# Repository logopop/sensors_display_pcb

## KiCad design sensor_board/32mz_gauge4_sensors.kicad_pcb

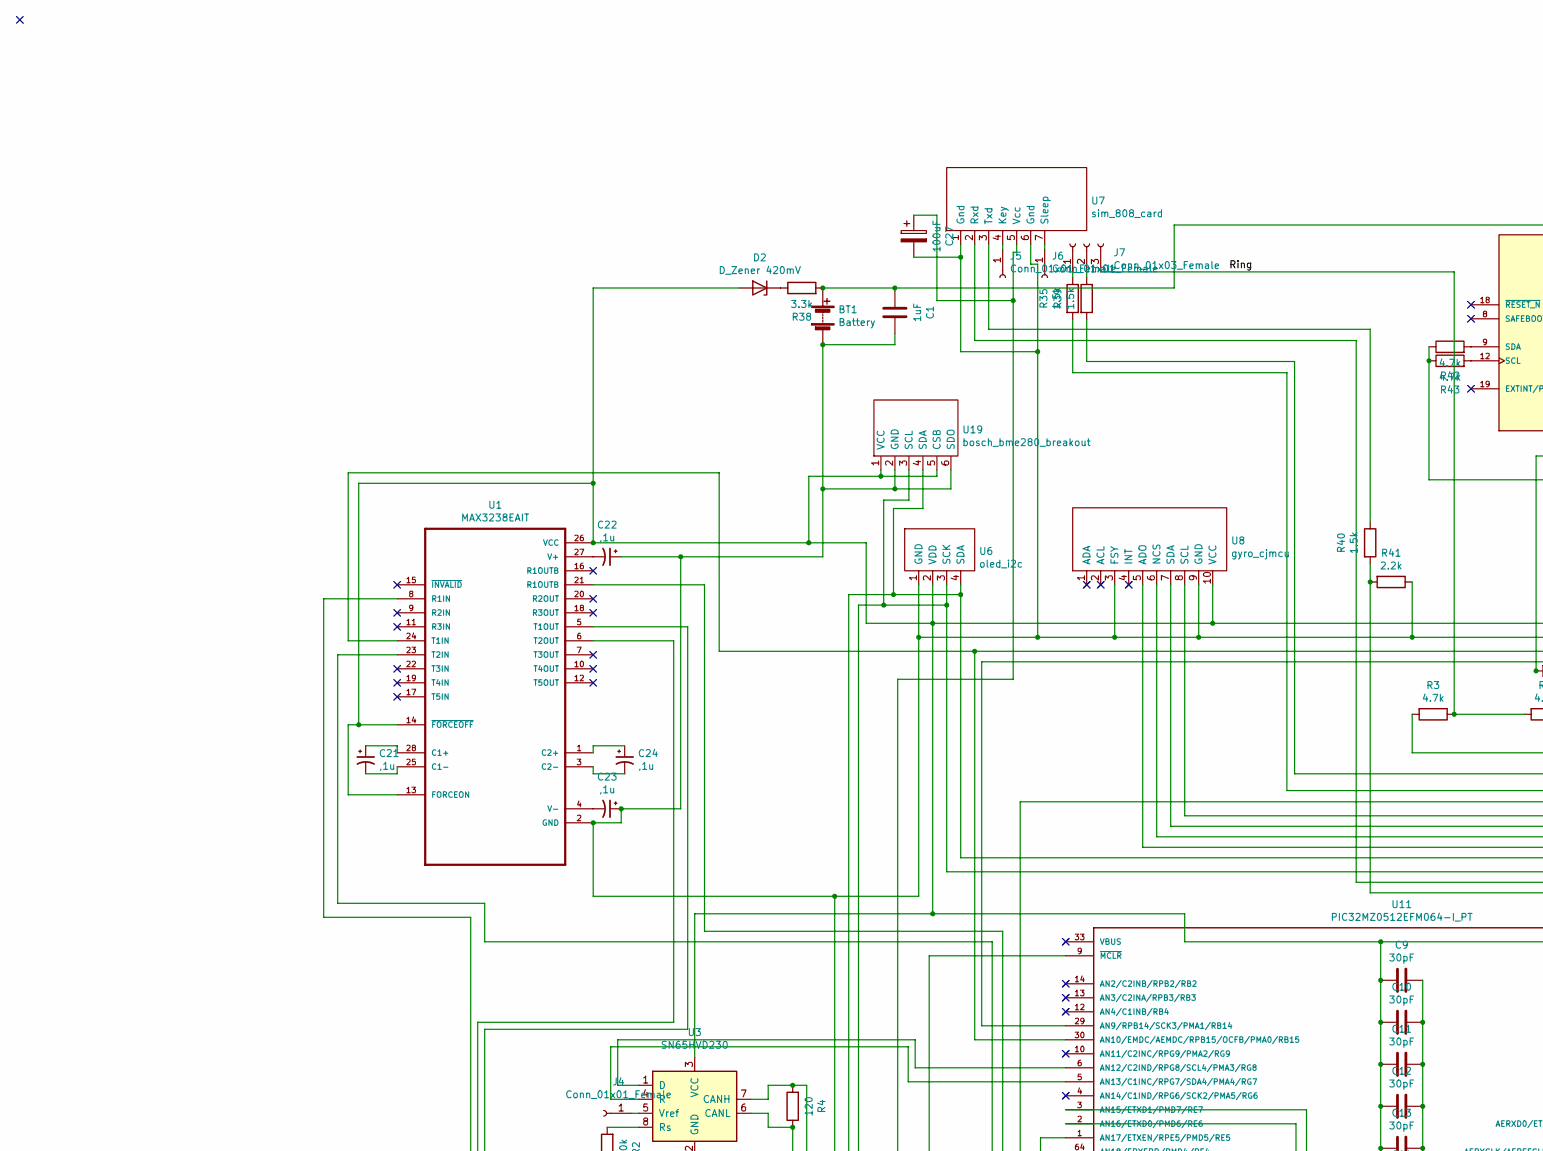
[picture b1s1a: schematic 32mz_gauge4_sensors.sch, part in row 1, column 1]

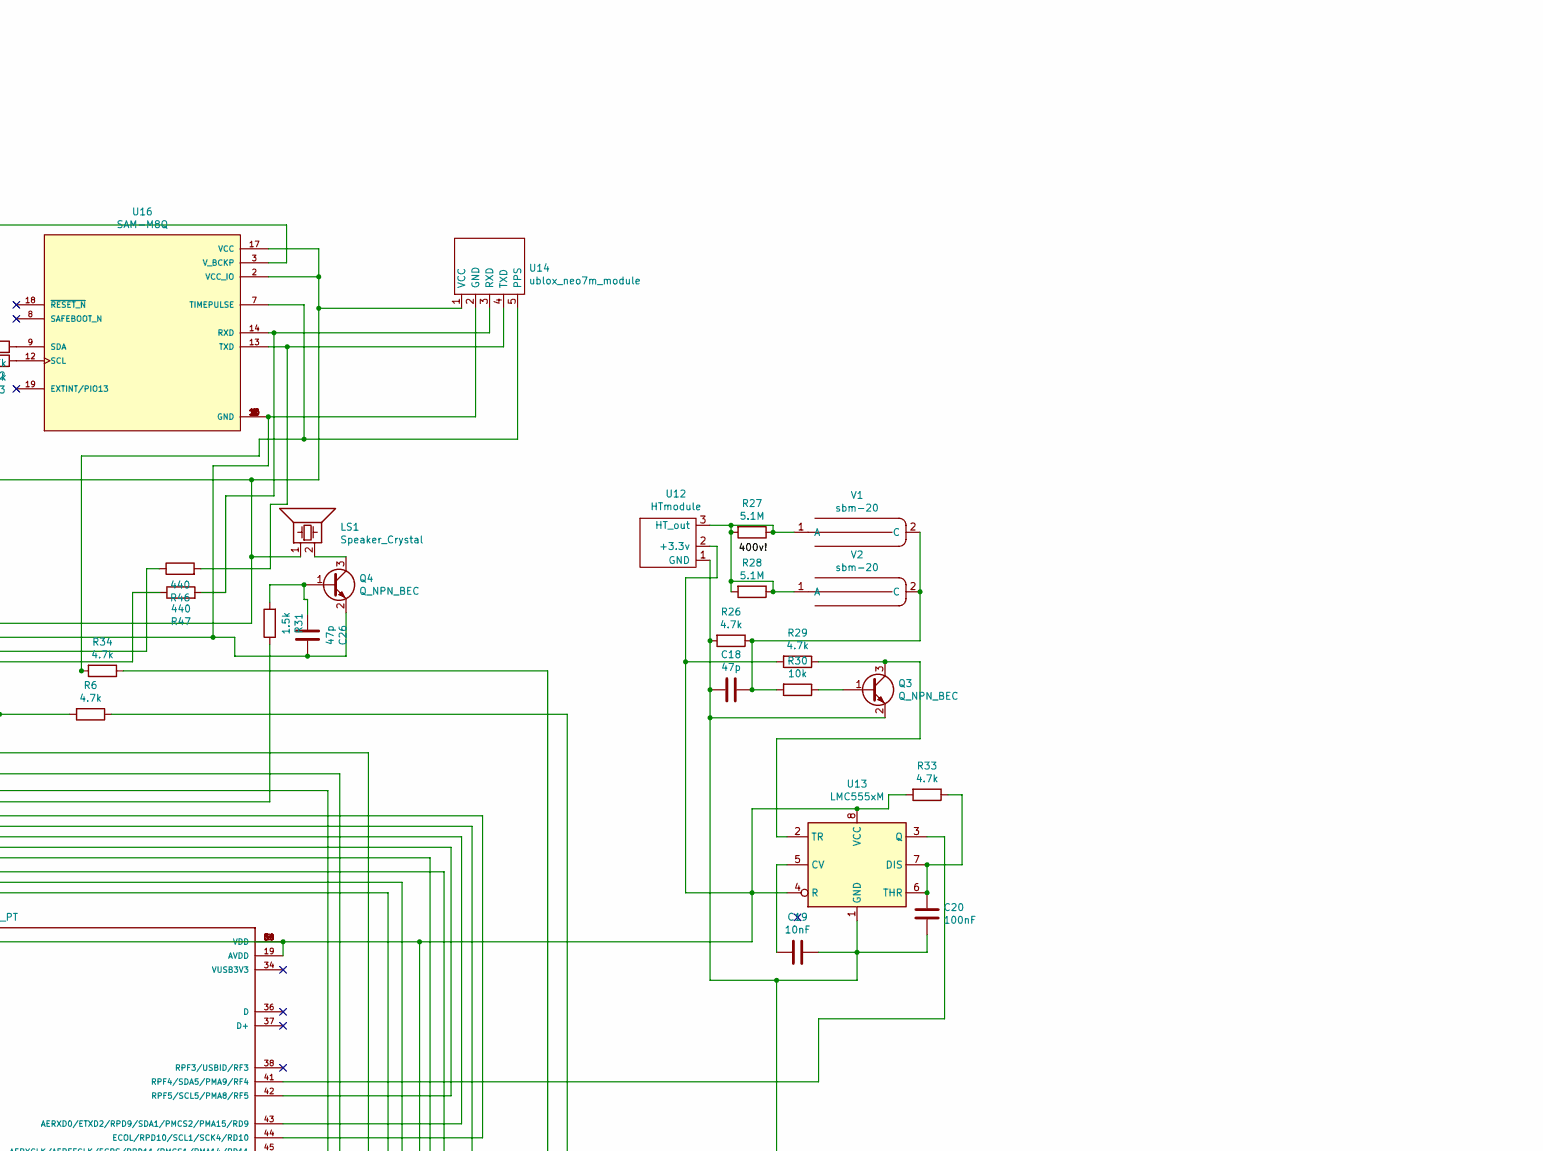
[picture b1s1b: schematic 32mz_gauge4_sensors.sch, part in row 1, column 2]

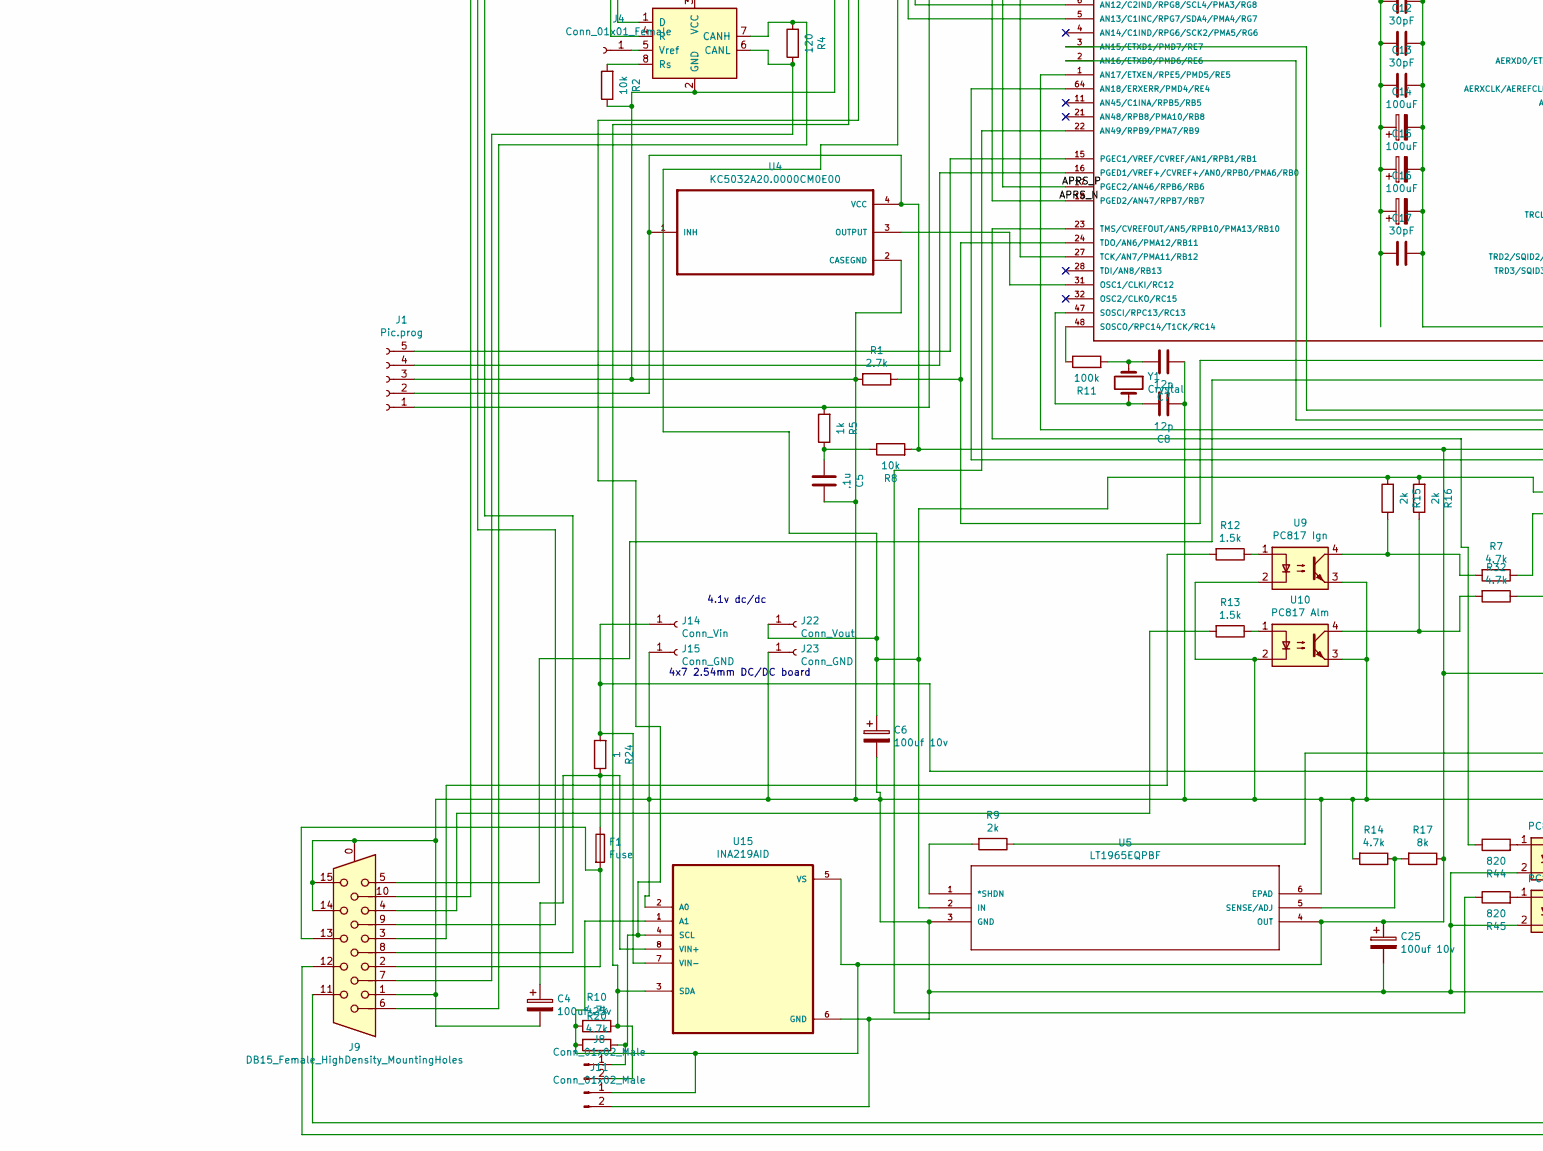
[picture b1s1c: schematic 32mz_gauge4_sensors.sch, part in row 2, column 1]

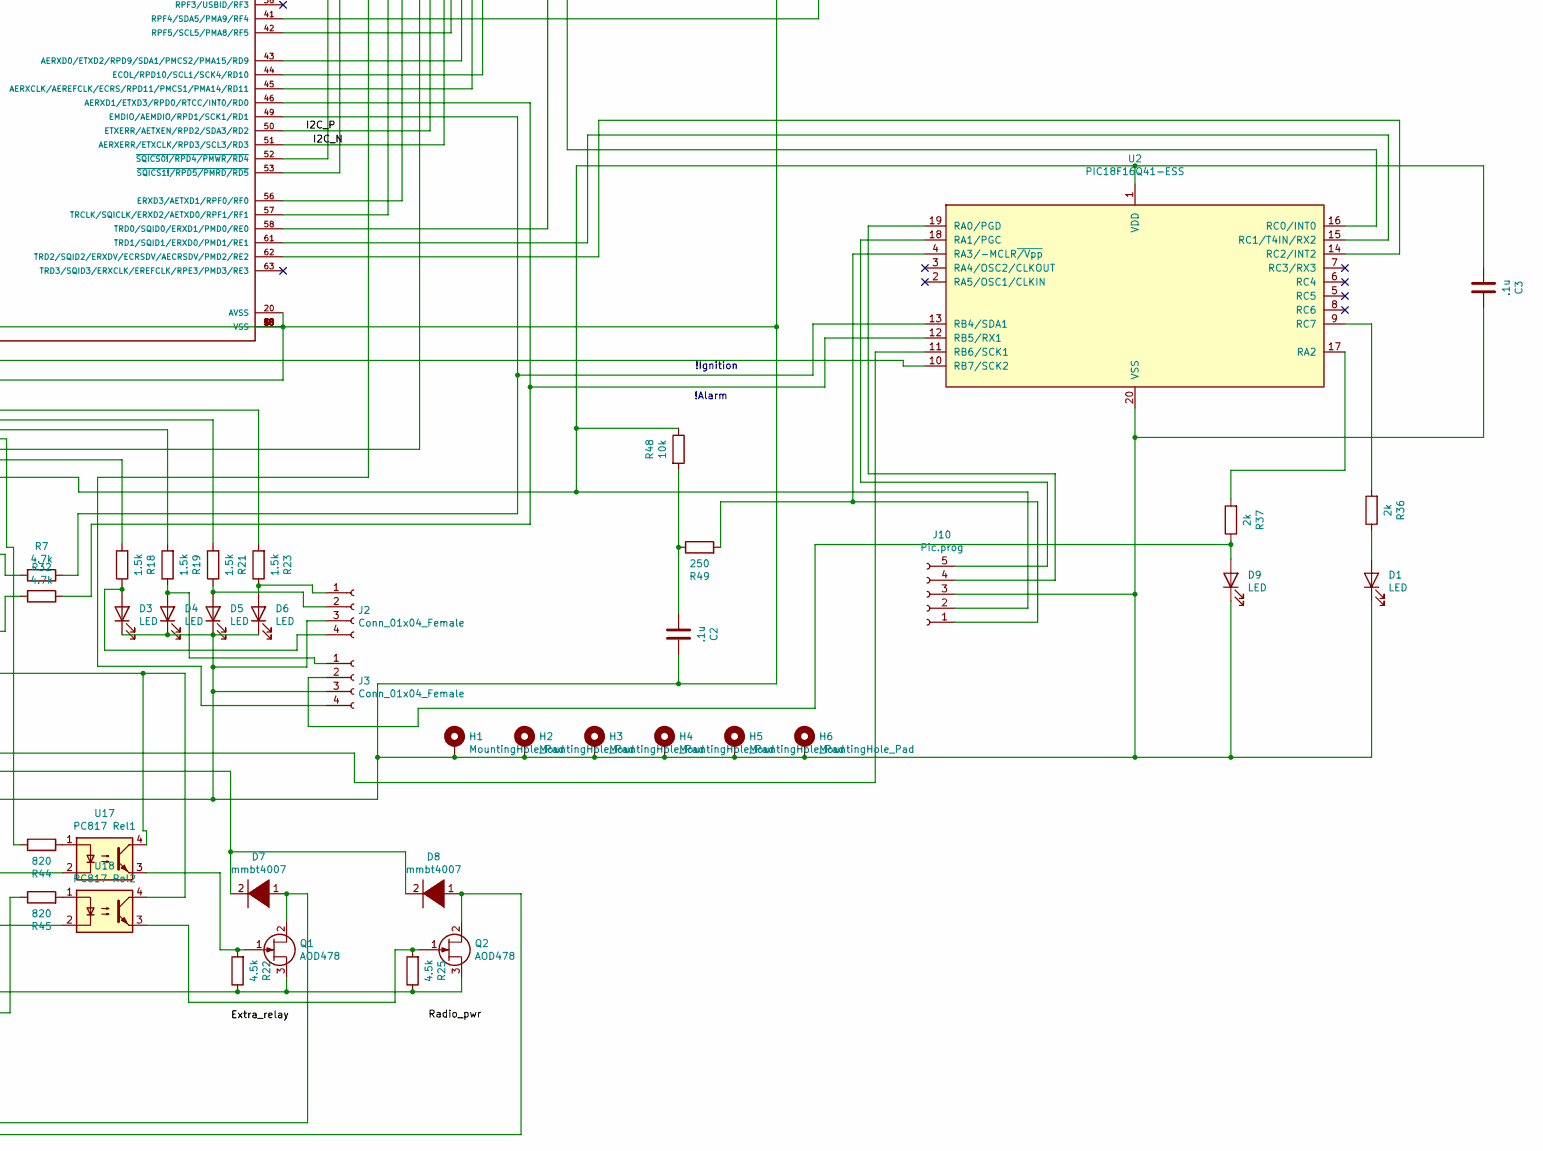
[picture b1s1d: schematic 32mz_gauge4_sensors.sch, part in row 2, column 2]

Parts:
BT1: Battery; batt_holder_1220
C1: 1uF; C_0805_2012Metric_Pad1.15x1.40mm_HandSolder
C2, C3, C5: .1u; C_0603_1608Metric_Pad1.05x0.95mm_HandSolder
C4: 100uf 25v; CP_EIA-6032-28_Kemet-C_Pad2.25x2.35mm_HandSolder
C6: 100uf 10v; CP_EIA-6032-20_AVX-F_Pad2.25x2.35mm_HandSolder
C7, C8: 12p; C_0603_HandSoldering
C9, C10, C11, C12, C13, C17: 30pF; C_0603_HandSoldering
C14, C15, C16, C27: 100uF; CP_EIA-6032-15_Kemet-U_Pad2.25x2.35mm_HandSolder
C18, C26: 47p; C_0603_HandSoldering
C19: 10nF; C_0603_HandSoldering
C20: 100nF; C_0603_HandSoldering
C21, C22, C23, C24: ,1u; C_1812_4532Metric_Pad1.30x3.40mm_HandSolder
C25: 100uf 10v; CP_EIA-6032-28_Kemet-C_Pad2.25x2.35mm_HandSolder
D1, D3, D4, D5, D6, D9: LED; LED_0603_1608Metric_Pad1.05x0.95mm_HandSolder
D2: D_Zener 420mV; D_1806_4516Metric_Pad1.57x1.80mm_HandSolder
D7, D8: mmbt4007; D_3220_8050Metric_Pad2.65x5.15mm_HandSolder
F1: Fuse; Fuseholder5x20_horiz_open_inline_Type-I
H1, H2, H3, H4, H5, H6: MountingHole_Pad; MountingHole_2.7mm_M2.5_ISO14580_Pad
J1: Pic.prog; Pin_Header_Straight_1x05_Pitch2.00mm
J2, J3: Conn_01x04_Female; PinHeader_1x04_P2.00mm_Vertical
J4: Conn_01x01_Female; Pin_Header_Straight_1x01_Pitch2.54mm
J5, J6: Conn_01x01_Female; PinHeader_1x01_P2.54mm_Vertical
J7: Conn_01x03_Female; PinHeader_1x03_P2.00mm_Vertical
J8, J11: Conn_01x02_Male; PinHeader_1x02_P2.54mm_Vertical
J9: DB15_Female_HighDensity_MountingHoles; DSUB-15-HD_Female_Horizontal_P2.29x1.98mm_EdgePinOffset3.03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
J10: Pic.prog; PinSocket_1x05_P2.00mm_Vertical
J14: Conn_Vin; PinHeader_1x01_P2.00mm_Vertical
J15, J23: Conn_GND; PinHeader_1x01_P2.00mm_Vertical
J22: Conn_Vout; PinHeader_1x01_P2.00mm_Vertical
LS1: Speaker_Crystal; Pin_Header_Straight_1x02_Pitch2.54mm
Q1, Q2: AOD478; TO-252-2
Q3, Q4: Q_NPN_BEC; SC-59_Handsoldering
R1: 2.7k; R_0805_2012Metric_Pad1.15x1.40mm_HandSolder
R2, R8, R30, R48: 10k; R_0805_2012Metric_Pad1.15x1.40mm_HandSolder
R3, R6, R7, R10, R14, R20, R26, R29, R32, R33, R34, R42, R43: 4.7k; R_0805_2012Metric_Pad1.15x1.40mm_HandSolder
R4: 120; R_0805_2012Metric_Pad1.15x1.40mm_HandSolder
R5: 1k; R_0805_2012Metric_Pad1.15x1.40mm_HandSolder
R9, R15, R16, R36, R37: 2k; R_0805_2012Metric_Pad1.15x1.40mm_HandSolder
R11: 100k; R_0805_2012Metric_Pad1.15x1.40mm_HandSolder
R12, R13, R18, R19, R21, R23, R31, R35, R39, R40: 1.5k; R_0805_2012Metric_Pad1.15x1.40mm_HandSolder
R17: 8k; R_0805_2012Metric_Pad1.15x1.40mm_HandSolder
R22, R25: 4.5k; R_0805_2012Metric_Pad1.15x1.40mm_HandSolder
R24: 1; R_2816_7142Metric_Pad3.20x4.45mm_HandSolder
R27, R28: 5.1M; R_0805_2012Metric_Pad1.15x1.40mm_HandSolder
R38: 3.3k; R_0805_2012Metric_Pad1.15x1.40mm_HandSolder
R41: 2.2k; R_0805_2012Metric_Pad1.15x1.40mm_HandSolder
R44, R45: 820; R_0805_2012Metric_Pad1.15x1.40mm_HandSolder
R46, R47: 440; R_0805_2012Metric_Pad1.15x1.40mm_HandSolder
R49: 250; R_0805_2012Metric_Pad1.15x1.40mm_HandSolder
U1: MAX3238EAIT; SSOP-28_5.3x10.2mm_Pitch0.65mm
U2: PIC18F16Q41-ESS; SSOP-20_5.3x7.2mm_P0.65mm_mod
U3: SN65HVD230; HTSOP-8-1EP_3.9x4.9mm_Pitch1.27mm_LargeCopper
U4: KC5032A20.0000CM0E00; Oscillator_SMD_EuroQuartz_XO53-4pin_5.0x3.2mm_HandSoldering
U5: LT1965EQPBF; DDPAK-5_Q
U6: oled_i2c; PinHeader_1x04_P2.54mm_Vertical
U7: sim_808_card; gsm_module_2
U8: gyro_cjmcu
U9: PC817 Ign; SOT254P975X400-4N
U10: PC817 Alm; SOT254P975X400-4N
U11: PIC32MZ0512EFM064-I_PT; TQFP-64-1EP_10x10mm_Pitch0.5mm
U12: HTmodule; HT_module
U13: LMC555xM; SOP-8_5.28x5.23mm_P1.27mm
U14: ublox_neo7m_module
U15: INA219AID; SOIC127P599X175-8N
U16: SAM-M8Q; XCVR_SAM-M8Q; PARTREV R06
U17: PC817 Rel1; SOT254P975X400-4N
U18: PC817 Rel2; SOT254P975X400-4N
U19: bosch_bme280_breakout
V1, V2: sbm-20; sbm_20
Y1: Crystal; Crystal_DS15_d1.5mm_l5.0mm_Vertical

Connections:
/APRS_N: U1.23 (T2IN), U11.18 (PGED2/AN47/RPB7/RB7)
/APRS_P: U1.21 (R1OUTB), U11.17 (PGEC2/AN46/RPB6/RB6)
/I2C_N: J8.1, R20.1, U6.3 (SCK), U11.51 (AERXERR/ETXCLK/RPD3/SCL3/RD3), U15.4 (SCL), U19.3 (SCL)
/I2C_P: J8.2, R10.1, U6.4 (SDA), U11.50 (ETXERR/AETXEN/RPD2/SDA3/RD2), U15.3 (SDA), U19.4 (SDA)
unnamed: BT1.1 (+), C1.1, R38.2, U16.3 (V_BCKP)
unnamed: BT1.2 (-), C1.2, C2.2, C3.2, C4.2, C5.2, C6.2, C7.1, C8.1, C9.2, C10.2, C11.2, C12.2, C13.2, C14.2, C15.2, C16.2, C17.2, C18.2, C19.1, C20.1, C22.1, C23.1, C25.2, C26.1, C27.2, D1.1 (K), D3.1 (K), D4.1 (K), D5.1 (K), D6.1 (K), D9.1 (K), H1.1, H2.1, H3.1, H4.1, H5.1, H6.1, J1.3, J2.3, J3.3, J9.0, J9.1, J9.5, J9.14, J9.15, J10.3, J11.2, J15.1, J23.1, Q1.3 (S), Q2.3 (S), Q3.2 (E), Q4.2 (E), R1.2, R2.1, R14.2, R22.1, R25.1, R26.2, R41.1, U1.2 (GND), U2.20 (VSS), U3.2 (GND), U4.2 (CASEGND), U5.3 (GND), U5.6 (EPAD), U6.1 (GND), U7.1 (Gnd), U7.6 (Gnd), U8.3 (FSY), U8.9 (GND), U9.2, U9.3, U10.2, U10.3, U11.7 (VSS), U11.20 (AVSS), U11.25 (VSS), U11.35 (VSS), U11.40 (VSS), U11.55 (VSS), U11.59 (VSS), U12.1 (GND), U13.1 (GND), U14.2 (GND), U15.2 (A0), U15.6 (GND), U16.1 (GND), U16.4 (GND), U16.5 (GND), U16.6 (GND), U16.10 (GND), U16.11 (GND), U16.15 (GND), U16.16 (GND), U16.20 (GND), U17.2, U18.2, U19.2 (GND), U19.6 (SDO)
unnamed: C2.1, R48.2, R49.1
unnamed: C4.1, F1.1, R24.1, U15.8 (VIN+)
unnamed: C5.1, R5.1, R8.1
unnamed: C7.2, R11.2, Y1.1
unnamed: C8.2, U11.47 (SOSCI/RPC13/RC13), Y1.2
unnamed: C9.1, C10.1, C11.1, C12.1, C13.1, C14.1, C15.1, C16.1, C17.1, C25.1, D2.2 (A), J1.2, J11.1, LS1.1, R8.2, R10.2, R17.1, R20.2, R29.2, R33.2, R42.1, R43.1, U1.13 (FORCEON), U1.14 (~FORCEOFF~), U1.26 (VCC), U3.3 (VCC), U4.1 (INH), U4.4 (VCC), U5.4 (OUT), U6.2 (VDD), U8.10 (VCC), U11.8 (VDD), U11.19 (AVDD), U11.26 (VDD), U11.39 (VDD), U11.54 (VDD), U11.60 (VDD), U12.2 (+3.3v), U13.4 (R), U13.8 (VCC), U14.1 (VCC), U15.1 (A1), U15.5 (VS), U16.2 (VCC_IO), U16.17 (VCC), U17.4, U18.4, U19.1 (VCC), U19.5 (CSB)
unnamed: C18.1, R26.1, R30.2, V1.2 (C), V2.2 (C)
unnamed: C19.2, U13.5 (CV)
unnamed: C20.2, R33.1, U13.6 (THR), U13.7 (DIS)
unnamed: C21.1, U1.28 (C1+)
unnamed: C21.2, U1.25 (C1-)
unnamed: C22.2, U1.27 (V+)
unnamed: C23.2, U1.4 (V-)
unnamed: C24.1, U1.1 (C2+)
unnamed: C24.2, U1.3 (C2-)
unnamed: C26.2, Q4.1 (B), R31.2
unnamed: C3.1, C6.1, C27.1, J10.2, J22.1, R15.2, R16.2, R48.1, U2.1 (VDD), U5.2 (IN), U7.5 (Vcc)
unnamed: D1.2 (A), R36.1
unnamed: D2.1 (K), R38.1
unnamed: D3.2 (A), J2.4, R18.1
unnamed: D4.2 (A), J3.1, R19.1
unnamed: D5.2 (A), J2.2, R21.1
unnamed: D6.2 (A), J2.1, R23.1
unnamed: D7.1 (K), J9.11, Q1.2 (D)
unnamed: D7.2 (A), D8.2 (A), J14.1, R24.2, U15.7 (VIN-)
unnamed: D8.1 (K), J9.12, Q2.2 (D)
unnamed: D9.2 (A), J3.2, R37.1
unnamed: F1.2, J9.2, J9.13
unnamed: J1.1, R5.2, U11.9 (~MCLR~)
unnamed: J1.4, U11.16 (PGED1/VREF+/CVREF+/AN0/RPB0/PMA6/RB0)
unnamed: J1.5, U11.15 (PGEC1/VREF/CVREF/AN1/RPB1/RB1)
unnamed: J3.4, R3.2
unnamed: J4.1, U3.5 (Vref)
unnamed: J5.1, U7.4 (Key)
unnamed: J6.1, U7.7 (Sleep)
unnamed: J7.1, R35.1
unnamed: J7.2, R39.1
unnamed: J7.3, R3.1, R6.2
unnamed: J9.3, R12.2
unnamed: J9.4, R13.2
unnamed: J9.6, R4.2, U3.7 (CANH)
unnamed: J9.7, R4.1, U3.6 (CANL)
unnamed: J9.8, U1.5 (T1OUT)
unnamed: J9.9, U1.6 (T2OUT)
unnamed: J9.10, U1.8 (R1IN)
unnamed: J10.1, R49.2, U2.4 (RA3/-MCLR~/Vpp)
unnamed: J10.4, U2.19 (RA0/PGD)
unnamed: J10.5, U2.18 (RA1/PGC)
unnamed: LS1.2, Q4.3 (C)
unnamed: Q1.1 (G), R22.2, U17.3
unnamed: Q2.1 (G), R25.2, U18.3
unnamed: Q3.1 (B), R30.1
unnamed: Q3.3 (C), R29.1, U13.2 (TR)
unnamed: R1.1, U2.10 (RB7/SCK2), U11.24 (TDO/AN6/PMA12/RB11)
unnamed: R2.2, U3.8 (Rs)
unnamed: R6.1, U2.16 (RC0/INT0)
unnamed: R7.1, U2.13 (RB4/SDA1), U11.49 (EMDIO/AEMDIO/RPD1/SCK1/RD1)
unnamed: R9.1, U2.11 (RB6/SCK1)
unnamed: R9.2, U5.1 (*SHDN)
unnamed: R11.1, U11.48 (SOSCO/RPC14/T1CK/RC14)
unnamed: R12.1, U9.1
unnamed: R13.1, U10.1
unnamed: R14.1, R17.2, U5.5 (SENSE/ADJ)
unnamed: R7.2, R15.1, U9.4
unnamed: R16.1, R32.2, U10.4
unnamed: R18.2, U11.64 (AN18/ERXERR/PMD4/RE4)
unnamed: R19.2, U11.1 (AN17/ETXEN/RPE5/PMD5/RE5)
unnamed: R21.2, U11.2 (AN16/ETXD0/PMD6/RE6)
unnamed: R23.2, U11.3 (AN15/ETXD1/PMD7/RE7)
unnamed: R27.1, R27.2, R28.1, R28.2, U12.3 (HT_out), V1.1 (A), V2.1 (A)
unnamed: R31.1, U11.27 (TCK/AN7/PMA11/RB12)
unnamed: R32.1, U2.12 (RB5/RX1), U11.46 (AERXD1/ETXD3/RPD0/RTCC/INT0/RD0)
unnamed: R34.1, U11.58 (TRD0/SQID0/ERXD1/PMD0/RE0)
unnamed: R34.2, U14.5 (PPS), U16.7 (TIMEPULSE)
unnamed: R35.2, U11.52 (~SQICS0!/RPD4/PMWR/RD4~)
unnamed: R36.2, U2.9 (RC7)
unnamed: R37.2, U2.17 (RA2)
unnamed: R39.2, U11.53 (~SQICS1!/RPD5/PMRD/RD5~)
unnamed: R40.1, U7.3 (Txd)
unnamed: R40.2, R41.2, U11.57 (TRCLK/SQICLK/ERXD2/AETXD0/RPF1/RF1)
unnamed: R42.2, U16.9 (SDA)
unnamed: R43.2, U16.12 (SCL)
unnamed: R44.1, U11.23 (TMS/CVREFOUT/AN5/RPB10/PMA13/RB10)
unnamed: R44.2, U17.1
unnamed: R45.1, U11.22 (AN49/RPB9/PMA7/RB9)
unnamed: R45.2, U18.1
unnamed: R46.1, U1.24 (T1IN), U11.30 (AN10/EMDC/AEMDC/RPB15/OCFB/PMA0/RB15)
unnamed: R46.2, U14.4 (TXD), U16.13 (TXD)
unnamed: R47.1, U11.29 (AN9/RPB14/SCK3/PMA1/RB14)
unnamed: R47.2, U14.3 (RXD), U16.14 (RXD)
unnamed: U3.4 (R), U11.5 (AN13/C1INC/RPG7/SDA4/PMA4/RG7)
unnamed: U3.1 (D), U11.6 (AN12/C2IND/RPG8/SCL4/PMA3/RG8)
unnamed: U4.3 (OUTPUT), U11.31 (OSC1/CLKI/RC12)
unnamed: U11.41 (RPF4/SDA5/PMA9/RF4), U13.3 (Q)
unnamed: U8.5 (ADO), U11.42 (RPF5/SCL5/PMA8/RF5)
unnamed: U8.6 (NCS), U11.43 (AERXD0/ETXD2/RPD9/SDA1/PMCS2/PMA15/RD9)
unnamed: U8.8 (SCL), U11.44 (ECOL/RPD10/SCL1/SCK4/RD10)
unnamed: U8.7 (SDA), U11.45 (AERXCLK/AEREFCLK/ECRS/RPD11/PMCS1/PMA14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)
unnamed: U7.2 (Rxd), U11.56 (ERXD3/AETXD1/RPF0/RF0)
unnamed: U2.15 (RC1/T4IN/RX2), U11.61 (TRD1/SQID1/ERXD0/PMD1/RE1)
unnamed: U2.14 (RC2/INT2), U11.62 (TRD2/SQID2/ERXDV/ECRSDV/AECRSDV/PMD2/RE2)

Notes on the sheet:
4x7 2.54mm DC/DC board
!Alarm
!Ignition
4.1v dc/dc

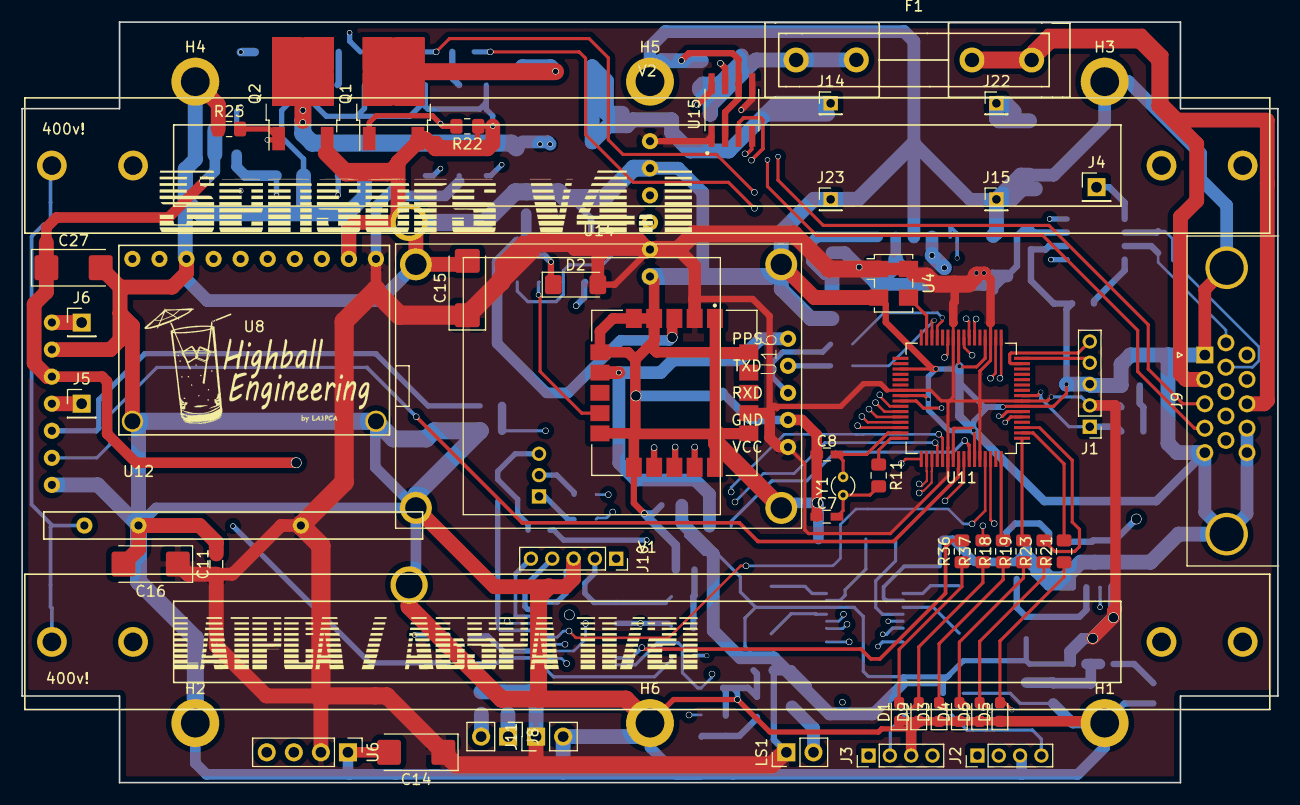
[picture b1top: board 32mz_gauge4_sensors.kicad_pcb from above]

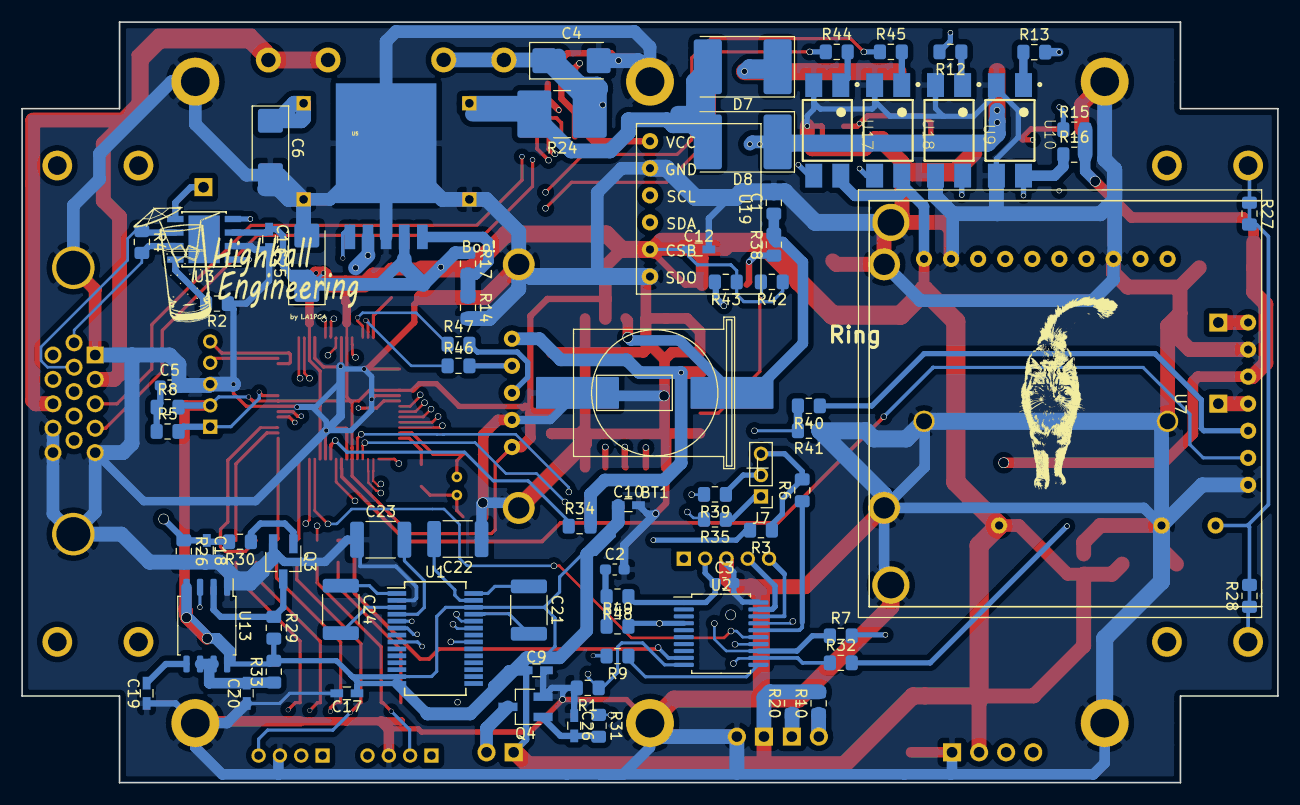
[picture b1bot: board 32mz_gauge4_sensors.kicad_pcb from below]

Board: 4 copper layers, 117.9 x 71.4 mm, 136 parts (78 on the bottom side), 107 nets.

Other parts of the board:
 : fry

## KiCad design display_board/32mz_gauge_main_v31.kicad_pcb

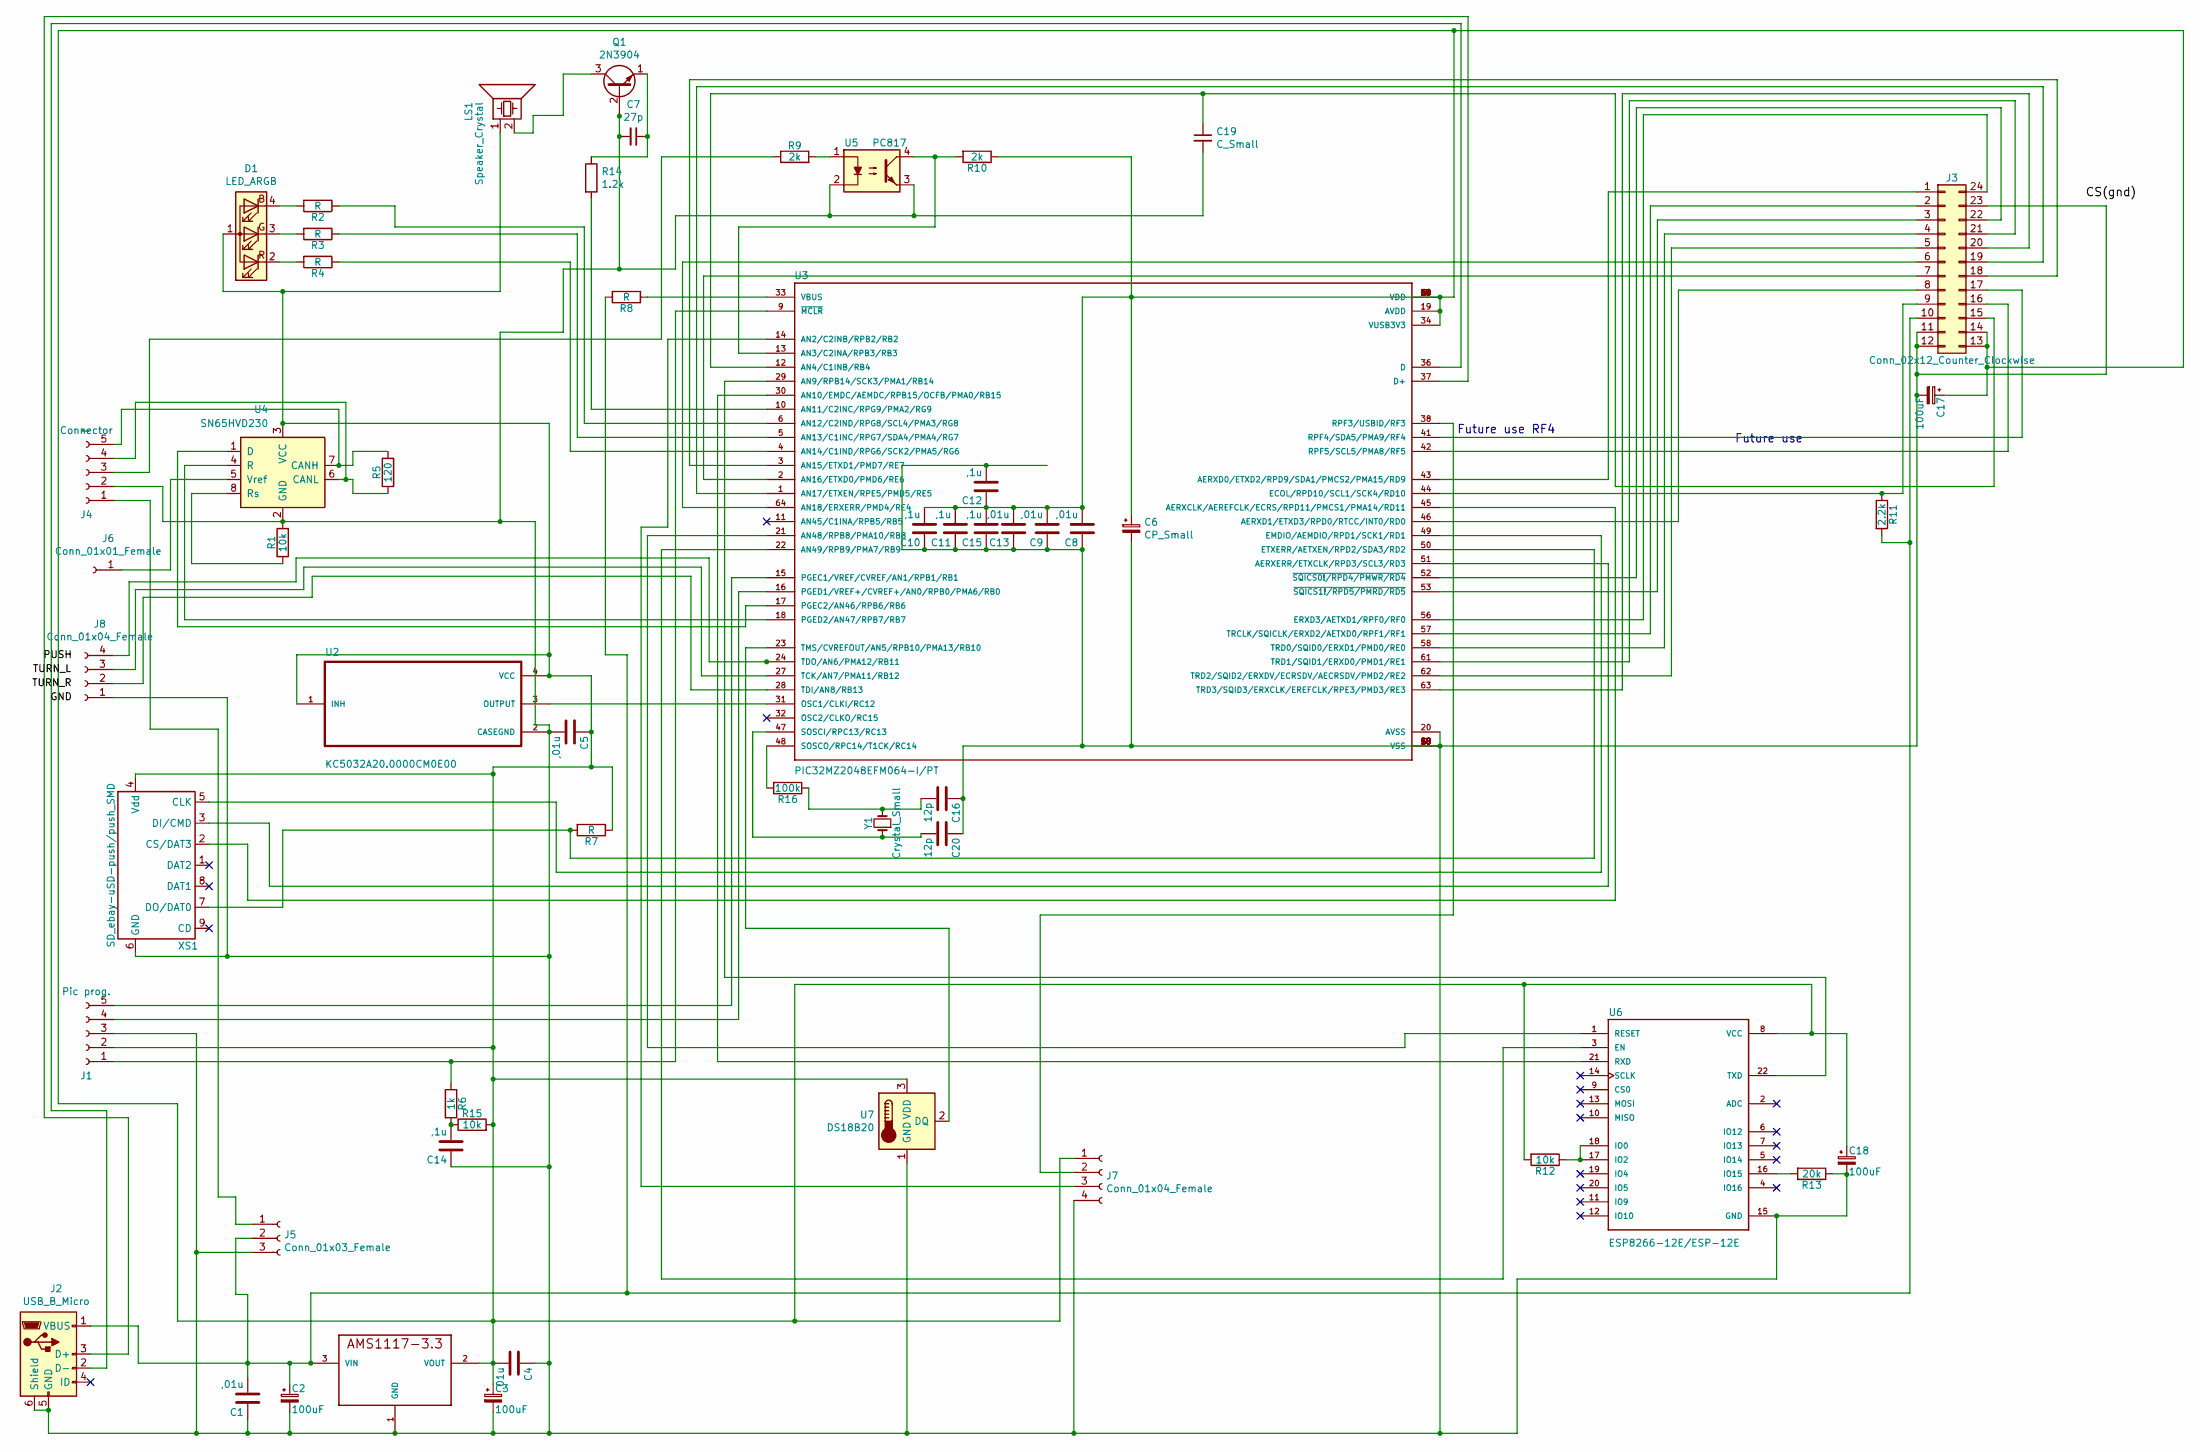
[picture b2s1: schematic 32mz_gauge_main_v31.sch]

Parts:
C1, C4, C5: ,01u; C_0805_HandSoldering
C2, C3: 100uF; CP_Elec_5x4.5
C6: CP_Small; CP_Tantalum_Case-A_EIA-3216-18_Hand
C7: 27p; C_0603_HandSoldering
C8, C9, C13: ,01u; C_0603_HandSoldering
C10, C11, C12, C14, C15: ,1u; C_0603_HandSoldering
C16, C20: 12p; C_0603_HandSoldering
C17, C18: 100uF; CP_Tantalum_Case-A_EIA-3216-18_Hand
C19: C_Small; C_0603_HandSoldering
D1: LED_ARGB; SM0605BCRG
J1: Pic prog.; Pin_Header_Straight_1x05_Pitch2.00mm
J2: USB_B_Micro; USB_Micro-B_Molex-105017-0001
J3: Conn_02x12_Counter_Clockwise; JAE_LY20-24P-2T_2x12x2.00mm_Straight
J4: Connector; JST_ZE_BM05B-ZESS-TBT_05x1.5mm_Straight
J5: Conn_01x03_Female; Pin_Header_Straight_1x03_Pitch2.54mm
J6: Conn_01x01_Female; Pin_Header_Straight_1x01_Pitch1.00mm
J7: Conn_01x04_Female; Pin_Header_Straight_1x04_Pitch2.00mm
J8: Conn_01x04_Female; JST_ZE_BM04B-ZESS-TBT_04x1.5mm_Straight
LS1: Speaker_Crystal; Pin_Header_Straight_1x02_Pitch2.00mm
Q1: 2N3904; SOT-23
R1, R12, R15: 10k; R_0603_HandSoldering
R2, R3, R4, R7, R8: R; R_0603_HandSoldering
R5: 120; R_0603_HandSoldering
R6: 1k; R_0603_HandSoldering
R9, R10: 2k; R_0603_HandSoldering
R11: 2.2k; R_0603_HandSoldering
R13: 20k; R_0603_HandSoldering
R14: 1.2k; R_0603_HandSoldering
R16: 100k; R_0603_HandSoldering
U1: AMS1117-3.3; SOT-223
U2: KC5032A20.0000CM0E00; Oscillator_SMD_EuroQuartz_XO53-4pin_5.0x3.2mm_HandSoldering
U3: PIC32MZ2048EFM064-I/PT; TQFP-64-1EP_10x10mm_Pitch0.5mm
U4: SN65HVD230; SOIC-8_3.9x4.9mm_Pitch1.27mm
U5: PC817; DIP-4_W7.62mm
U6: ESP8266-12E/ESP-12E; XCVR_ESP8266-12E%2fESP-12E
U7: DS18B20; TO-92_Inline_Narrow_Oval
XS1: SD_ebay-uSD-push/push_SMD; Conn_uSDcard
Y1: Crystal_Small; Crystal_C26-LF_d2.1mm_l6.5mm_Vertical

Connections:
unnamed: C1.1, C2.2, C3.2, C4.1, C5.2, C6.2, C7.2, C8.1, C9.1, C10.1, C11.1, C12.2, C13.1, C14.1, C15.1, C16.1, C17.2, C18.2, C19.2, C20.1, J1.3, J2.5 (GND), J2.6 (Shield), J3.11, J3.12, J3.23, J4.2, J5.3, J7.4, J8.1, Q1.2 (B), R1.2, R13.1, U1.1 (GND), U2.2 (CASEGND), U3.7 (VSS), U3.20 (AVSS), U3.25 (VSS), U3.35 (VSS), U3.40 (VSS), U3.55 (VSS), U3.59 (VSS), U4.2 (GND), U5.2, U5.3, U6.15 (GND), U7.1 (GND), XS1.6 (GND)
unnamed: C1.2, C2.1, J2.1 (VBUS), J3.10, J5.2, R8.2, R11.2, U1.3 (VIN)
unnamed: C7.1, Q1.1 (E), R14.1
unnamed: C3.1, C4.2, C5.1, C6.1, C8.2, C9.2, C10.2, C11.2, C12.1, C13.2, C15.2, C17.1, C18.1, D1.1 (A), J1.2, J3.13, J3.14, J7.1, LS1.1, R7.1, R10.1, R12.2, R15.2, U1.2 (VOUT), U1.4, U2.1 (INH), U2.4 (VCC), U3.8 (VDD), U3.19 (AVDD), U3.26 (VDD), U3.34 (VUSB3V3), U3.39 (VDD), U3.54 (VDD), U3.60 (VDD), U4.3 (VCC), U6.8 (VCC), U7.3 (VDD), XS1.4 (Vdd)
unnamed: C14.2, R6.2, R15.1
unnamed: C16.2, R16.1, Y1.2
unnamed: C19.1, J3.15, U3.12 (AN4/C1INB/RB4)
unnamed: C20.2, U3.47 (SOSCI/RPC13/RC13), Y1.1
unnamed: D1.2 (RK), R4.2
unnamed: D1.3 (GK), R3.2
unnamed: D1.4 (BK), R2.2
unnamed: J1.1, R6.1, U3.9 (~MCLR~)
unnamed: J1.4, U3.16 (PGED1/VREF+/CVREF+/AN0/RPB0/PMA6/RB0)
unnamed: J1.5, U3.15 (PGEC1/VREF/CVREF/AN1/RPB1/RB1)
unnamed: J2.2 (D-), U3.36 (D)
unnamed: J2.3 (D+), U3.37 (D+)
unnamed: J3.1, U3.43 (AERXD0/ETXD2/RPD9/SDA1/PMCS2/PMA15/RD9)
unnamed: J3.2, U3.57 (TRCLK/SQICLK/ERXD2/AETXD0/RPF1/RF1)
unnamed: J3.3, U3.53 (~SQICS1!/RPD5/PMRD/RD5~)
unnamed: J3.4, U3.58 (TRD0/SQID0/ERXD1/PMD0/RE0)
unnamed: J3.5, U3.62 (TRD2/SQID2/ERXDV/ECRSDV/AECRSDV/PMD2/RE2)
unnamed: J3.6, U3.64 (AN18/ERXERR/PMD4/RE4)
unnamed: J3.7, U3.2 (AN16/ETXD0/PMD6/RE6)
unnamed: J3.8, U3.46 (AERXD1/ETXD3/RPD0/RTCC/INT0/RD0)
unnamed: J3.9, R11.1, U3.44 (ECOL/RPD10/SCL1/SCK4/RD10)
unnamed: J3.16, U3.42 (RPF5/SCL5/PMA8/RF5)
unnamed: J3.17, U3.41 (RPF4/SDA5/PMA9/RF4)
unnamed: J3.18, U3.3 (AN15/ETXD1/PMD7/RE7)
unnamed: J3.19, U3.1 (AN17/ETXEN/RPE5/PMD5/RE5)
unnamed: J3.20, U3.63 (TRD3/SQID3/ERXCLK/EREFCLK/RPE3/PMD3/RE3)
unnamed: J3.21, U3.61 (TRD1/SQID1/ERXD0/PMD1/RE1)
unnamed: J3.22, U3.52 (~SQICS0!/RPD4/PMWR/RD4~)
unnamed: J3.24, U3.56 (ERXD3/AETXD1/RPF0/RF0)
unnamed: J4.1, J5.1
unnamed: J4.3, R9.1
unnamed: J4.4, R5.1, U4.6 (CANL)
unnamed: J4.5, R5.2, U4.7 (CANH)
unnamed: J6.1, U4.5 (Vref)
unnamed: J7.2, U3.38 (RPF3/USBID/RF3)
unnamed: J7.3, U3.14 (AN2/C2INB/RPB2/RB2)
unnamed: J8.2, U3.28 (TDI/AN8/RB13)
unnamed: J8.3, U3.27 (TCK/AN7/PMA11/RB12)
unnamed: J8.4, U3.24 (TDO/AN6/PMA12/RB11)
unnamed: LS1.2, Q1.3 (C)
unnamed: R1.1, U4.8 (Rs)
unnamed: R2.1, U3.6 (AN12/C2IND/RPG8/SCL4/PMA3/RG8)
unnamed: R3.1, U3.5 (AN13/C1INC/RPG7/SDA4/PMA4/RG7)
unnamed: R4.1, U3.4 (AN14/C1IND/RPG6/SCK2/PMA5/RG6)
unnamed: R7.2, U3.50 (ETXERR/AETXEN/RPD2/SDA3/RD2), XS1.7 (DO/DAT0)
unnamed: R8.1, U3.33 (VBUS)
unnamed: R9.2, U5.1
unnamed: R10.2, U3.13 (AN3/C2INA/RPB3/RB3), U5.4
unnamed: R12.1, U6.17 (IO2), U6.18 (IO0)
unnamed: R13.2, U6.16 (IO15)
unnamed: R14.2, U3.10 (AN11/C2INC/RPG9/PMA2/RG9)
unnamed: R16.2, U3.48 (SOSCO/RPC14/T1CK/RC14)
unnamed: U2.3 (OUTPUT), U3.31 (OSC1/CLKI/RC12)
unnamed: U3.17 (PGEC2/AN46/RPB6/RB6), U4.1 (D)
unnamed: U3.18 (PGED2/AN47/RPB7/RB7), U4.4 (R)
unnamed: U3.21 (AN48/RPB8/PMA10/RB8), U6.1 (RESET)
unnamed: U3.22 (AN49/RPB9/PMA7/RB9), U6.3 (EN)
unnamed: U3.23 (TMS/CVREFOUT/AN5/RPB10/PMA13/RB10), U7.2 (DQ)
unnamed: U3.29 (AN9/RPB14/SCK3/PMA1/RB14), U6.22 (TXD)
unnamed: U3.30 (AN10/EMDC/AEMDC/RPB15/OCFB/PMA0/RB15), U6.21 (RXD)
unnamed: U3.45 (AERXCLK/AEREFCLK/ECRS/RPD11/PMCS1/PMA14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), XS1.2 (CS/DAT3)
unnamed: U3.49 (EMDIO/AEMDIO/RPD1/SCK1/RD1), XS1.5 (CLK)
unnamed: U3.51 (AERXERR/ETXCLK/RPD3/SCL3/RD3), XS1.3 (DI/CMD)

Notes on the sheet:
Future use
Future use RF4
